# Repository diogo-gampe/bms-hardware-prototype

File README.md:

## Desenvolvimento em KICAD de placa de avaliação do CI da Texas Instrumets BQ769x2 para monitoramento e proteção de batérias de íon-lítio 3S-16S.

## Changelog

12/12/25
- Separa folha de monitoramento, folha de proteção e folha raiz
- (Folha raiz)Adiciona conector para resistores shunt de simulação de células
- (Folha de monitoramento) Adiciona botão de WAKE no pino TS2 do CI e jumper para conectar termistor externo ao pino TS2
- (Folha de monitoramento) Adiciona conector para monitorar externamente tensões geradas por regulador interno do CI em REG1 e REG2.
- (Folha de proteção) Adiciona componentes para circuito de disparo de fusível controlável
- (Folha de proteção) Adiciona componentes para circuito de pré-carga/descarga
- (Folha de proteção) Adciona componentes para proteção de conexão com polaridade reversa

18/12/25
- Adiciona diretório com simulações de LTSpice
28/01/25
- Adiciona footprints finais, com base na lista de componentes fornecidas ao pessoal do SENAI
- Posiciona Net-Tie entre terminal negativo da bateria e tensão de referência dos CIs para isolar caminhos de alta corrente
30/01/25
- Posiciona footprints de testpoints para medições de sinais chave para testes. 
- Ajusta posicionamento de regiões de alta corrente.

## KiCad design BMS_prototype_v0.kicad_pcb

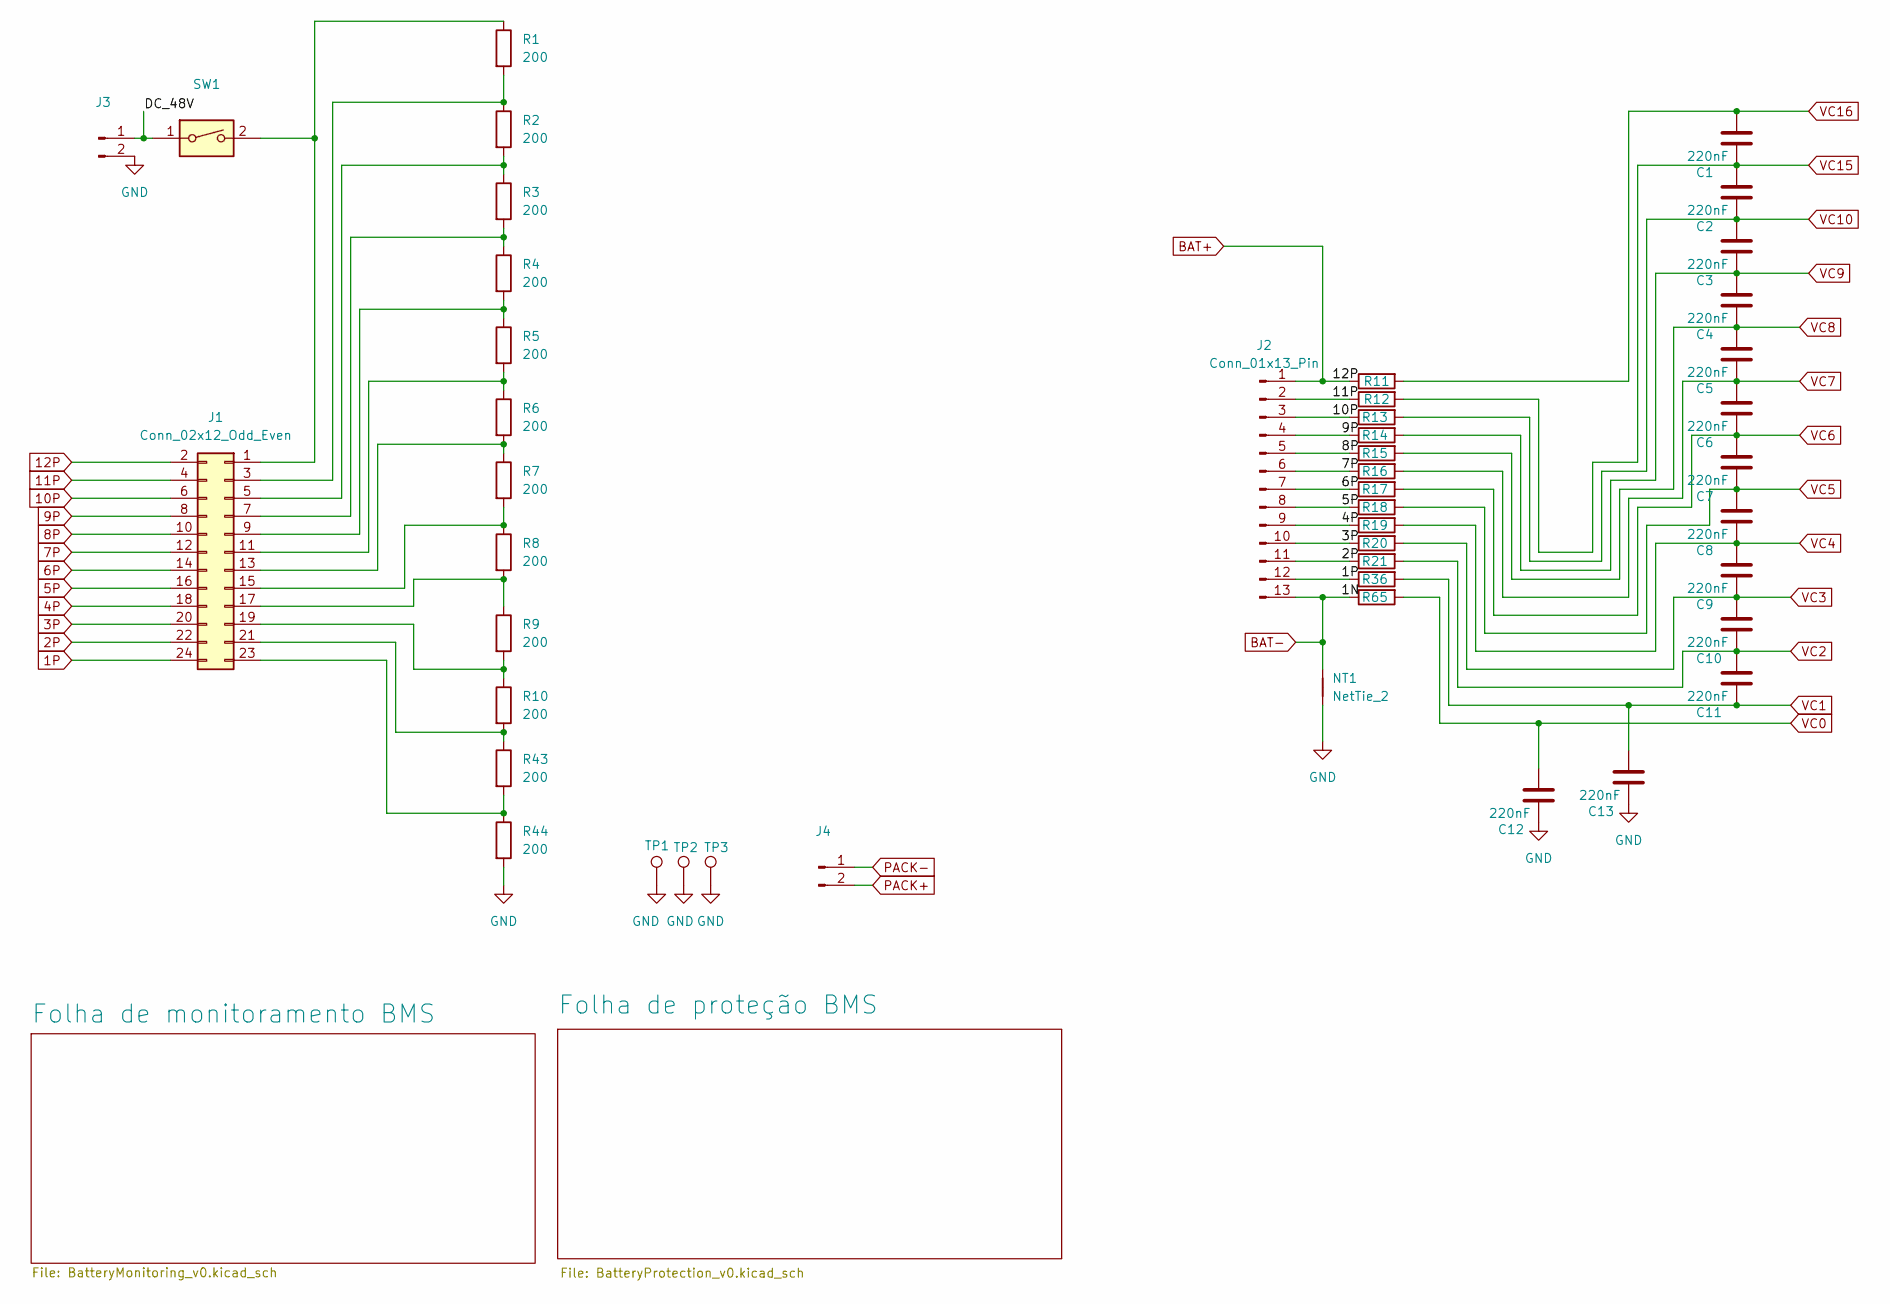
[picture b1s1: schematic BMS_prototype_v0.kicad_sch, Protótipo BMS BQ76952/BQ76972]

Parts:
C1, C2, C3, C4, C5, C6, C7, C8, C9, C10, C11, C12, C13: 220nF; C_1206_3216Metric_Pad1.33x1.80mm_HandSolder; Manufacturer_Part_Number C1206C224J5RECAUTO
J1: Conn_02x12_Odd_Even; PinHeader_2x12_P2.54mm_Vertical; Manufacturer_Part_Number G800W268018EU
J2: Conn_01x13_Pin; PinHeader_1x13_P2.54mm_Vertical; Manufacturer_Part_Number PH1-13-UA
J3: Conn_01x02_Pin; PinHeader_1x02_P2.54mm_Vertical; Manufacturer_Part_Number G800W306018EU
J4: Conn_01x02_Pin; CONN_1935776_PXC; Manufacturer_Part_Number G800W306018EU
NT1: NetTie_2; NetTie-2_SMD_Pad0.5mm
R1, R2, R3, R4, R5, R6, R7, R8, R9, R10, R43, R44: 200; R_1206_3216Metric; Manufacturer_Part_Number CR1206-FX-2000ELF
R11, R12, R13, R14, R15, R16, R17, R18, R19, R20, R21, R36, R65: 20; R_1206_3216Metric; Manufacturer_Part_Number RC1206FR-0720RL
SW1: SW_DIP_x01; SWT31AAA3S1; Manufacturer_Part_Number SW-T3-1A-A-A3-S1
TP1, TP2, TP3: TestPoint; TestPoint_Pad_3.0x3.0mm

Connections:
1P: J1.24, J2.12, R36.1
2P: J1.22, J2.11, R21.1
3P: J1.20, J2.10, R20.1
4P: J1.18, J2.9, R19.1
5P: J1.16, J2.8, R18.1
6P: J1.14, J2.7, R17.1
7P: J1.12, J2.6, R16.1
8P: J1.10, J2.5, R15.1
9P: J1.8, J2.4, R14.1
10P: J1.6, J2.3, R13.1
11P: J1.4, J2.2, R12.1
12P: J1.2, J2.1, R11.1; also elsewhere on the board
/DC_48V: J3.1, SW1.1
BAT-: J2.13, NT1.2, R65.1; also elsewhere on the board
GND: C12.2, C13.2, J3.2, NT1.1, R44.2, TP1.1, TP2.1, TP3.1; also elsewhere on the board
unnamed: J1.1, R1.1, SW1.2
unnamed: J1.3, R1.2, R2.1
unnamed: J1.5, R2.2, R3.1
unnamed: J1.7, R3.2, R4.1
unnamed: J1.9, R4.2, R5.1
unnamed: J1.11, R5.2, R6.1
unnamed: J1.13, R6.2, R7.1
unnamed: J1.15, R7.2, R8.1
unnamed: J1.17, R8.2, R9.1
unnamed: J1.19, R9.2, R10.1
unnamed: J1.21, R10.2, R43.1
unnamed: J1.23, R43.2, R44.1
PACK+: J4.2; also elsewhere on the board
PACK-: J4.1; also elsewhere on the board
VC0: C12.1, R65.2; also elsewhere on the board
VC1: C11.2, C13.1, R36.2; also elsewhere on the board
VC2: C10.2, C11.1, R21.2; also elsewhere on the board
VC3: C9.2, C10.1, R20.2; also elsewhere on the board
VC4: C8.2, C9.1, R19.2; also elsewhere on the board
VC5: C7.2, C8.1, R18.2; also elsewhere on the board
VC6: C6.2, C7.1, R17.2; also elsewhere on the board
VC7: C5.2, C6.1, R16.2; also elsewhere on the board
VC8: C4.2, C5.1, R15.2; also elsewhere on the board
VC9: C3.2, C4.1, R14.2; also elsewhere on the board
VC10: C2.2, C3.1, R13.2; also elsewhere on the board
VC15: C1.2, C2.1, R12.2; also elsewhere on the board
VC16: C1.1, R11.2; also elsewhere on the board

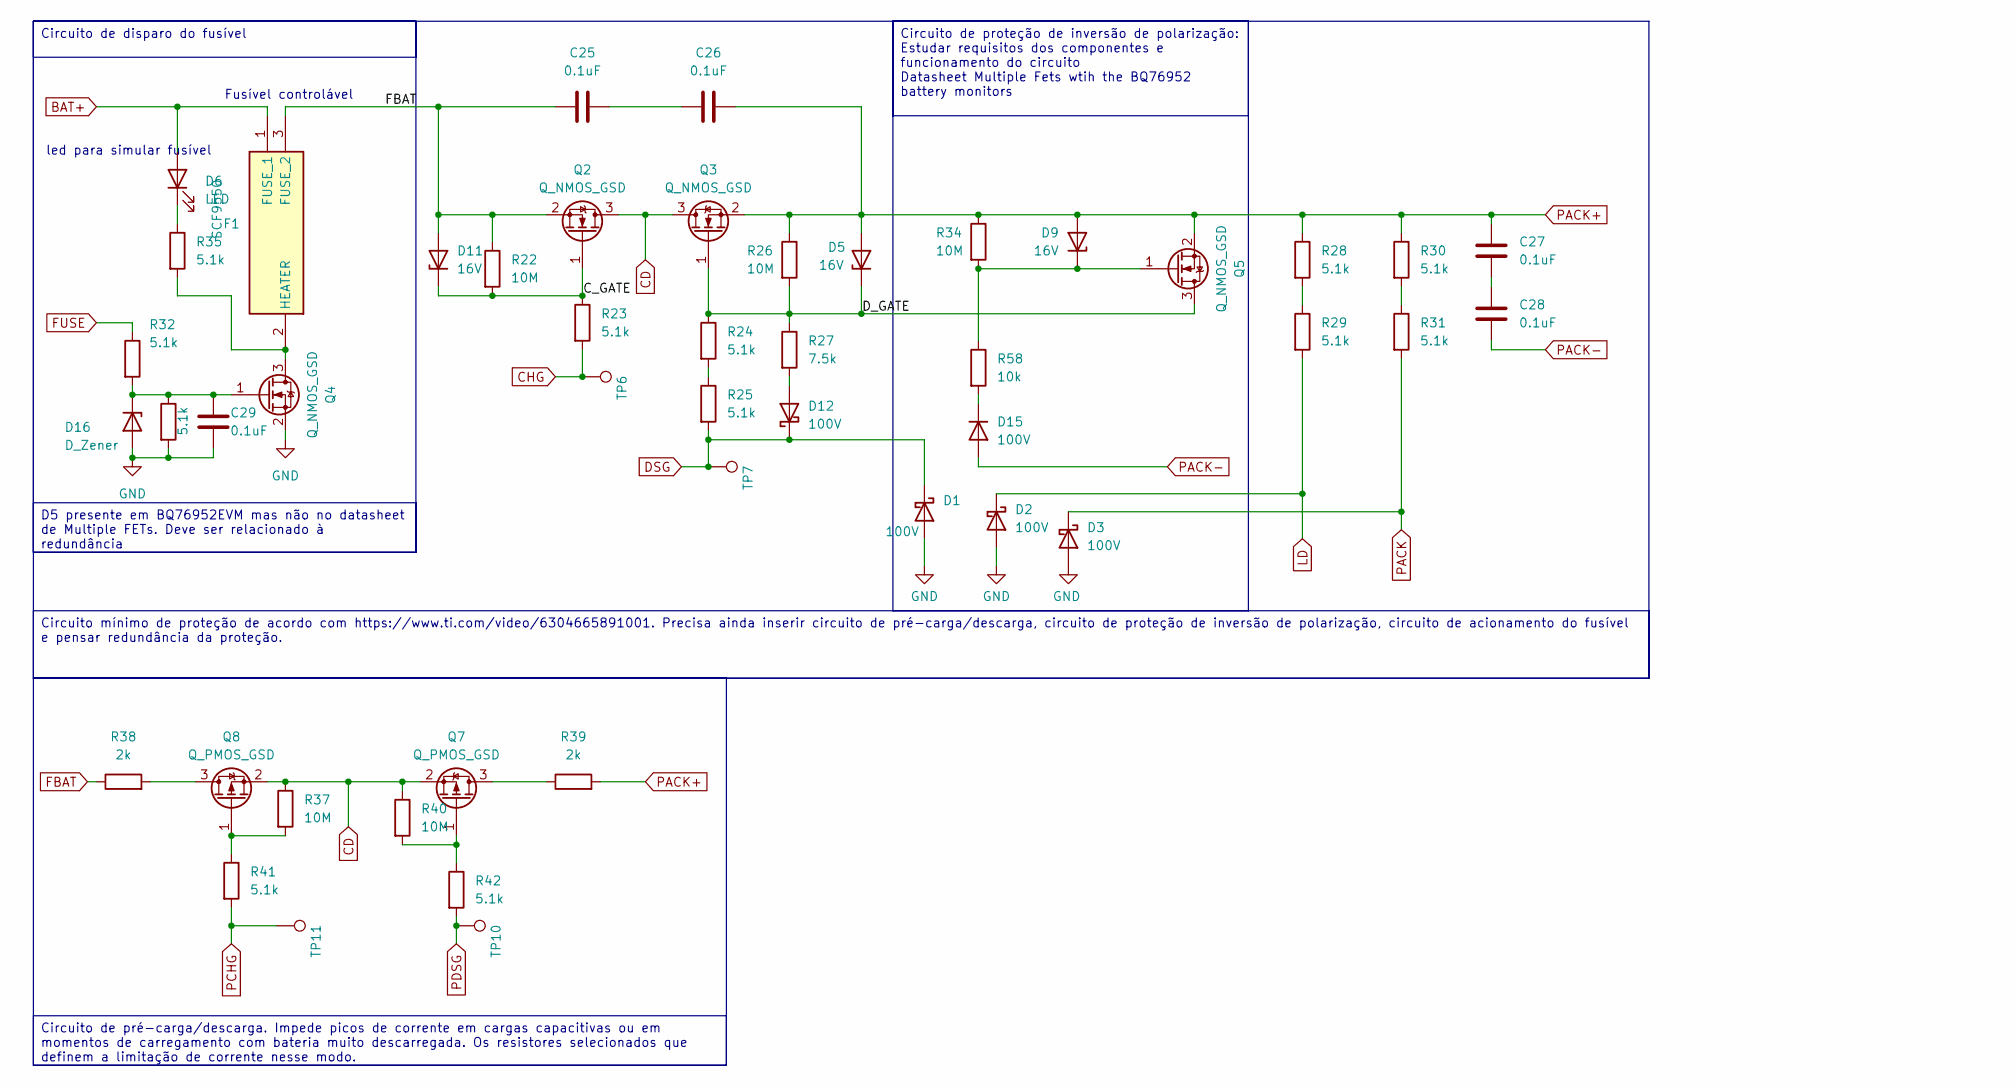
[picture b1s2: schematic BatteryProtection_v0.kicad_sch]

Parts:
C25, C26, C27, C28, C29: 0.1uF; C_1206_3216Metric_Pad1.33x1.80mm_HandSolder; Manufacturer_Part_Number C1206C104K5RACTU
D1, D2, D3, D12: 100V; D_SOD-123; Manufacturer_Part_Number BAT46W-7-F
D5, D9, D11: 16V; D_SOD-123; Manufacturer_Part_Number MMSZ5246B-TP
D6: LED; LED_1210_3225Metric; Manufacturer_Part_Number SML-LX1210IGC-TR
D15: 100V; SOT-23; Manufacturer_Part_Number MMBD914LT3G
D16: D_Zener; D_SOD-123; Manufacturer_Part_Number MMSZ4697T1G
F1: SCF9550; Sem título; Mouser Part Number 650-ITV4030L1412NR
Q2, Q3, Q5: Q_NMOS_GSD; TO-252-3_TabPin2; Manufacturer_Part_Number IPD200N15N3GATMA1
Q4: Q_NMOS_GSD; TO-252-3_TabPin2; Manufacturer_Part_Number AOD256
Q7, Q8: Q_PMOS_GSD; TSOP-6_1.65x3.05mm_P0.95mm; Manufacturer_Part_Number SI3437DV-T1-GE3
R22, R26, R34, R37, R40: 10M; R_1206_3216Metric; Manufacturer_Part_Number HV732BTTD1005F
R23, R24, R25, R28, R29, R30, R31, R32, R33, R35, R41, R42: 5.1k; R_1206_3216Metric; Manufacturer_Part_Number CRCW12065K10FKEAHP
R27: 7.5k; R_1206_3216Metric; Manufacturer_Part_Number RNCP1206FTD7K50
R38, R39: 2k; R_1206_3216Metric; Manufacturer_Part_Number HRG3216P-2001-D-T1
R58: 10k; R_1206_3216Metric; Manufacturer_Part_Number ERJ-8GEYJ103V
TP6, TP7, TP10, TP11: TestPoint; TestPoint_Loop_D3.80mm_Drill2.5mm

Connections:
12P: D6.2 (A), F1.1 (FUSE_1); also elsewhere on the board
/Folha de proteção BMS/C_GATE: D11.1 (K), Q2.1 (G), R22.2, R23.1
/Folha de proteção BMS/D_GATE: D5.1 (K), Q3.1 (G), Q5.3 (D), R24.1, R26.2, R27.1
CD: Q2.3 (D), Q3.3 (D), Q7.2 (S), Q8.2 (S), R37.1, R40.1; also elsewhere on the board
CHG: R23.2, TP6.1; also elsewhere on the board
DSG: D1.1 (K), D12.1 (K), R25.2, TP7.1; also elsewhere on the board
FBAT: C25.1, D11.2 (A), F1.3 (FUSE_2), Q2.2 (S), R22.1, R38.1
FUSE: R32.1; also elsewhere on the board
GND: C29.1, D1.2 (A), D2.2 (A), D3.2 (A), D16.2 (A), Q4.2 (S), R33.2; also elsewhere on the board
LD: D2.1 (K), R29.2; also elsewhere on the board
unnamed: C25.2, C26.1
unnamed: C27.1, C28.2
unnamed: D6.1 (K), R35.1
unnamed: D9.1 (K), Q5.1 (G), R34.2, R58.1
unnamed: D12.2 (A), R27.2
unnamed: D15.1 (K), R58.2
unnamed: C29.2, D16.1 (K), Q4.1 (G), R32.2, R33.1
unnamed: F1.2 (HEATER), Q4.3 (D), R35.2
unnamed: Q7.3 (D), R39.1
unnamed: Q7.1 (G), R40.2, R42.1
unnamed: Q8.3 (D), R38.2
unnamed: Q8.1 (G), R37.2, R41.1
unnamed: R24.2, R25.1
unnamed: R28.2, R29.1
unnamed: R30.2, R31.1
PACK: D3.1 (K), R31.2; also elsewhere on the board
PACK+: C26.2, C27.2, D5.2 (A), D9.2 (A), Q3.2 (S), Q5.2 (S), R26.1, R28.1, R30.1, R34.1, R39.2; also elsewhere on the board
PACK-: C28.1, D15.2 (A); also elsewhere on the board
PCHG: R41.2, TP11.1; also elsewhere on the board
PDSG: R42.2, TP10.1; also elsewhere on the board

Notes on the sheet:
led para simular fusível
Fusível controlável
Circuito de proteção de inversão de polarização: Estudar requisitos dos componentes e funcionamento do circuito Datasheet Multiple Fets wtih the BQ76952 battery monitors
Circuito mínimo de proteção de acordo com https://www.ti.com/video/6304665891001. Precisa ainda inserir circuito de pré-carga/descarga, circuito de proteção de inversão de polarização, circuito de acionamento do fusível e pensar redundância da proteção.
D5 presente em BQ76952EVM mas não no datasheet de Multiple FETs. Deve ser relacionado à redundância
Circuito de disparo do fusível
Circuito de pré-carga/descarga. Impede picos de corrente em cargas capacitivas ou em momentos de carregamento com bateria muito descarregada. Os resistores selecionados que definem a limitação de corrente nesse modo.

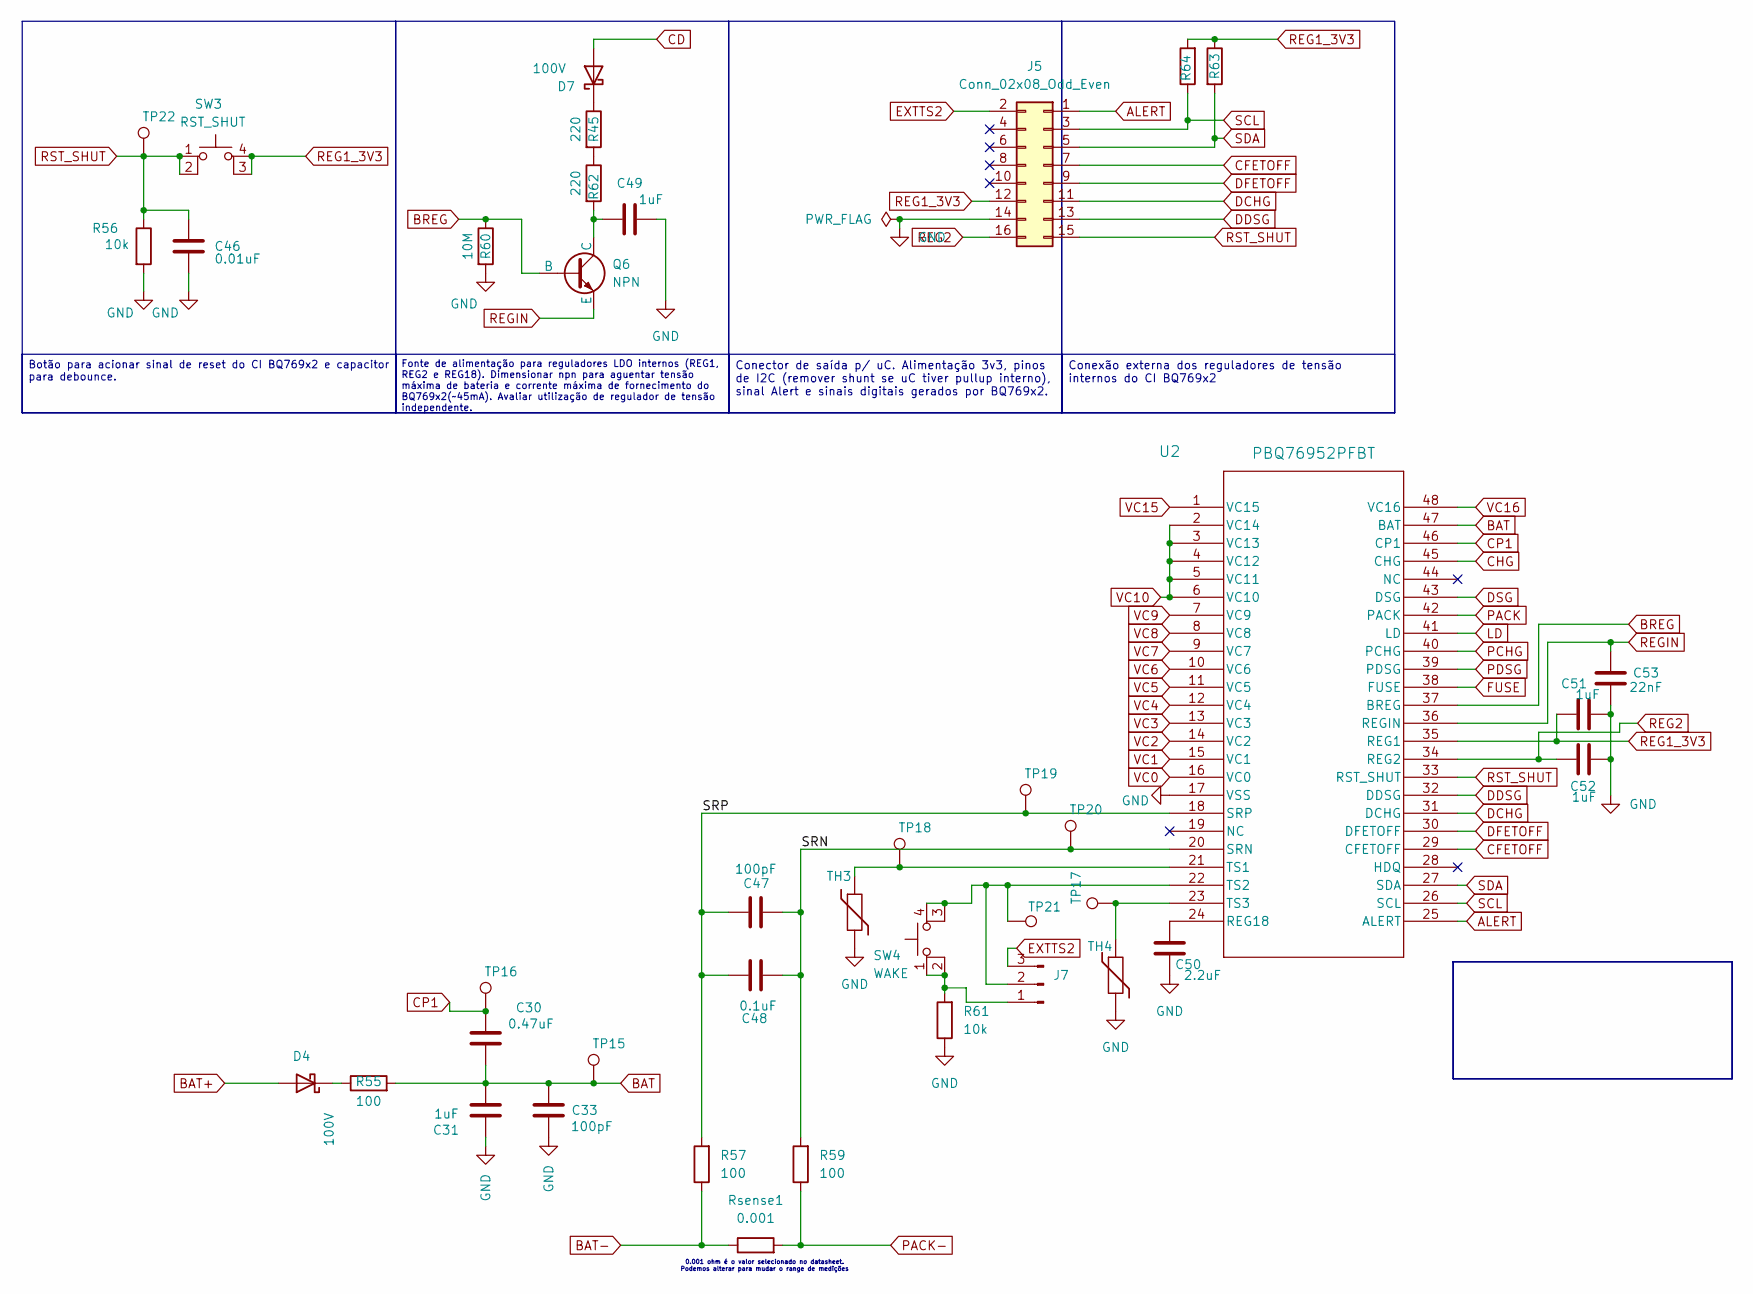
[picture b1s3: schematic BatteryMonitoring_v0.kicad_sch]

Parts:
C30: 0.47uF; C_1206_3216Metric_Pad1.33x1.80mm_HandSolder; Manufacturer_Part_Number CL31B474KBHNNNE
C31, C49, C51, C52: 1uF; C_1206_3216Metric_Pad1.33x1.80mm_HandSolder; Manufacturer_Part_Number CL31B105KBHNNNE
C33, C47: 100pF; C_1206_3216Metric_Pad1.33x1.80mm_HandSolder; Manufacturer_Part_Number VPDD102W101K1GV001E
C46: 0.01uF; C_1206_3216Metric_Pad1.33x1.80mm_HandSolder; Manufacturer_Part_Number 1206PC103KAT2A
C48: 0.1uF; C_1206_3216Metric_Pad1.33x1.80mm_HandSolder; Manufacturer_Part_Number C1206C104K5RACTU
C50: 2.2uF; C_1206_3216Metric_Pad1.33x1.80mm_HandSolder; Manufacturer_Part_Number CL31B225KBHNNNE
C53: 22nF; C_1206_3216Metric_Pad1.33x1.80mm_HandSolder; Manufacturer_Part_Number CC1206JRNPO9BN223
D4, D7: 100V; D_SOD-123; Manufacturer_Part_Number BAT46W-7-F
J5: Conn_02x08_Odd_Even; CONN16_SBH11-PBPC-D08-ST-BK_SUL; Manufacturer_Part_Number SBH11-PBPC-D08-ST-BK
J7: Conn_01x03_Pin; PinSocket_1x03_P2.54mm_Vertical; Manufacturer_Part_Number 2011-1X03G00SB-1
Q6: NPN; TO-92; Manufacturer_Part_Number 2N5830
R45, R62: 220; R_1206_3216Metric; Manufacturer_Part_Number CRCW2512220RJNEG
R55, R57, R59: 100; R_1206_3216Metric; Manufacturer_Part_Number RC1206FR-07100RL
R56, R61: 10k; R_1206_3216Metric; Manufacturer_Part_Number ERJ-8GEYJ103V
R60: 10M; R_1206_3216Metric; Manufacturer_Part_Number HV732BTTD1005F
R63, R64: 20; R_1206_3216Metric; Manufacturer_Part_Number RC1206FR-0720RL
Rsense1: 0.001; S200_75
SW3: RST_SHUT; SMT_FS; Manufacturer_Part_Number PTS526SM15SMTR2 LFS
SW4: WAKE; SMT_FS; Manufacturer_Part_Number PTS526SK15SMTR2 LFS
TH3, TH4: Thermistor; 103AT2; Manufacturer_Part_Number 103AT-2
TP15, TP16, TP17, TP18, TP19, TP20, TP21, TP22: TestPoint; TestPoint_Loop_D3.80mm_Drill2.5mm
U2: PBQ76952PFBT; BQ7692_TEX; Manufacturer_Part_Number BQ7695202PFBR

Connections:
12P: D4.2 (A); also elsewhere on the board
/Folha de monitoramento BMS/SRN: C47.2, C48.2, R59.2, TP20.1, U2.20 (SRN)
/Folha de monitoramento BMS/SRP: C47.1, C48.1, R57.2, TP19.1, U2.18 (SRP)
ALERT: J5.1, U2.25 (ALERT)
BAT: C30.2, C31.1, C33.1, R55.2, TP15.1, U2.47 (BAT)
BAT-: R57.1, Rsense1.1; also elsewhere on the board
BREG: Q6.2 (B), R60.1, U2.37 (BREG)
CD: D7.2 (A); also elsewhere on the board
CFETOFF: J5.7, U2.29 (CFETOFF)
CHG: U2.45 (CHG); also elsewhere on the board
CP1: C30.1, TP16.1, U2.46 (CP1)
DCHG: J5.11, U2.31 (DCHG)
DDSG: J5.13, U2.32 (DDSG)
DFETOFF: J5.9, U2.30 (DFETOFF)
DSG: U2.43 (DSG); also elsewhere on the board
EXTTS2: J5.2, J7.3
FUSE: U2.38 (FUSE); also elsewhere on the board
GND: C31.2, C33.2, C46.2, C49.2, C50.1, C51.1, C52.1, C53.2, J5.14, R56.2, R60.2, R61.1, TH3.2, TH4.2, U2.17 (VSS); also elsewhere on the board
LD: U2.41 (LD); also elsewhere on the board
unnamed: D4.1 (K), R55.1
unnamed: D7.1 (K), R45.1
unnamed: J7.1, R61.2, SW4.1, SW4.2
unnamed: J7.2, SW4.3 (K), SW4.4 (A), TP21.1, U2.22 (TS2)
unnamed: C49.1, Q6.1 (C), R62.2
unnamed: R45.2, R62.1
unnamed: C50.2, U2.24 (REG18)
unnamed: TH3.1, TP18.1, U2.21 (TS1)
unnamed: TH4.1, TP17.1, U2.23 (TS3)
PACK: U2.42 (PACK); also elsewhere on the board
PACK-: R59.1, Rsense1.2; also elsewhere on the board
PCHG: U2.40 (PCHG); also elsewhere on the board
PDSG: U2.39 (PDSG); also elsewhere on the board
REG1_3V3: C51.2, J5.12, R63.1, R64.2, SW3.3 (K), SW3.4 (A), U2.35 (REG1)
REG2: C52.2, J5.16, U2.34 (REG2)
REGIN: C53.1, Q6.3 (E), U2.36 (REGIN)
RST_SHUT: C46.1, J5.15, R56.1, SW3.1, SW3.2, TP22.1, U2.33 (RST_SHUT)
SCL: J5.3, R64.1, U2.26 (SCL)
SDA: J5.5, R63.2, U2.27 (SDA)
VC0: U2.16 (VC0); also elsewhere on the board
VC1: U2.15 (VC1); also elsewhere on the board
VC2: U2.14 (VC2); also elsewhere on the board
VC3: U2.13 (VC3); also elsewhere on the board
VC4: U2.12 (VC4); also elsewhere on the board
VC5: U2.11 (VC5); also elsewhere on the board
VC6: U2.10 (VC6); also elsewhere on the board
VC7: U2.9 (VC7); also elsewhere on the board
VC8: U2.8 (VC8); also elsewhere on the board
VC9: U2.7 (VC9); also elsewhere on the board
VC10: U2.2 (VC14), U2.3 (VC13), U2.4 (VC12), U2.5 (VC11), U2.6 (VC10); also elsewhere on the board
VC15: U2.1 (VC15); also elsewhere on the board
VC16: U2.48 (VC16); also elsewhere on the board

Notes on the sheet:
0.001 ohm é o valor selecionado no datasheet. Podemos alterar para mudar o range de medições
Conector de saída p/ uC. Alimentação 3v3, pinos de I2C (remover shunt se uC tiver pullup interno), sinal Alert e sinais digitais gerados por BQ769x2.
Botão para acionar sinal de reset do CI BQ769x2 e capacitor para debounce.
Conexão externa dos reguladores de tensão internos do CI BQ769x2
Fonte de alimentação para reguladores LDO internos (REG1, REG2 e REG18). Dimensionar npn para aguentar tensão máxima de bateria e corrente máxima de fornecimento do BQ769x2(~45mA). Avaliar utilização de regulador de tensão independente.

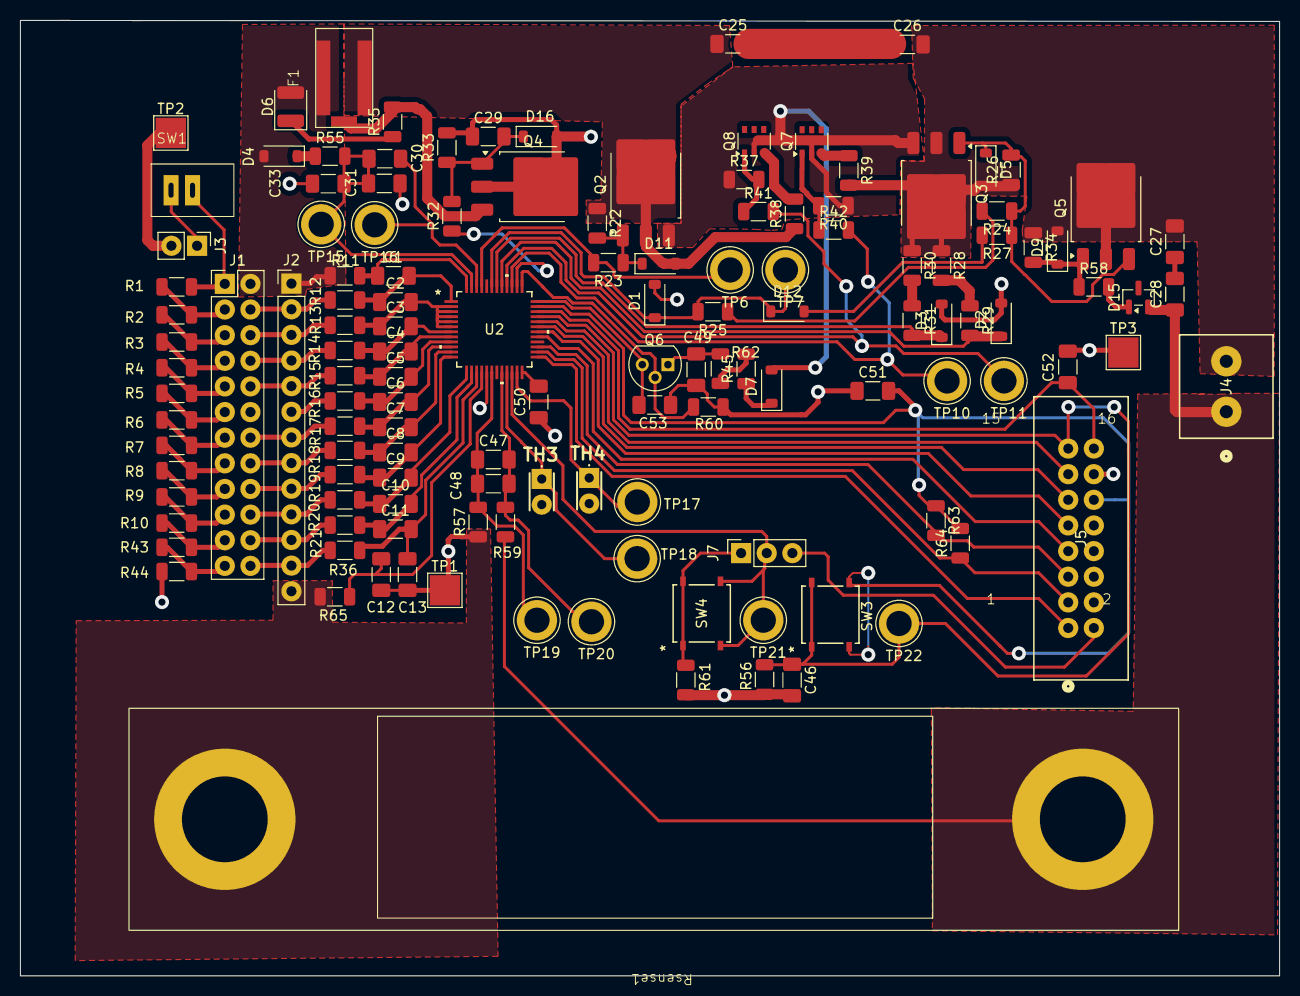
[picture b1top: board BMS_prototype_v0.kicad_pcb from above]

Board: 2 copper layers, 124.8 x 94.7 mm, 134 parts (0 on the bottom side), 94 nets.

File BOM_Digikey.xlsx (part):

Reference | Value | Qty | Digikey Link | Manufacturer_Part_Number
 | STM32H745ZIT3 | 5 | https://www.digikey.ca/en/products/detail/stmicroelectronics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 | STM32H745ZIT3
 | BQ76972PFBR | 5 | https://www.digikey.ca/en/products/detail/texas-instruments/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 | BQ7697202PFBR
U2 | BQ7695202PFBR | 5 | https://www.digikey.ca/en/products/detail/texas-instruments/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 | BQ7695202PFBR
 | TJA1044BT/0Z | 5 | https://www.digikey.ca/en/products/detail/nxp-usa-inc/TJA104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 | TJA1044BT/0Z
C47 | 100pF | 5 | https://www.digikey.ca/en/products/detail/johanson-dielectri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 | VPDD102W101K1GV001E
C33 | 100pF | 5 | https://www.digikey.ca/en/products/detail/johanson-dielectri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 | VPDD102W101K1GV001E
SW1 | SW_DIP_x01 | 5 | https://www.digikey.ca/en/products/detail/adam-tech/SW-T3-1A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 | SW-T3-1A-A-A3-S1
D6 | LED | 5 | https://www.digikey.ca/en/products/detail/lumex-opto-compone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 | SML-LX1210IGC-TR
Q8 | Q_PMOS_GSD | 5 | https://www.digikey.ca/en/products/detail/vishay-siliconix/S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 | SI3437DV-T1-GE3
Q7 | Q_PMOS_GSD | 5 | https://www.digikey.ca/en/products/detail/vishay-siliconix/S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 | SI3437DV-T1-GE3
J5 | Conn_02x08_Odd_Even | 5 | https://www.digikey.ca/en/products/detail/sullins-connector-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 | SBH11-PBPC-D08-ST-BK
R27 | 7.5k | 5 | https://www.digikey.ca/en/products/detail/stackpole-electron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 | RNCP1206FTD7K50
R59 | 100 | 5 | https://www.digikey.ca/en/products/detail/yageo/RC1206FR-071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 | RC1206FR-07100RL
R57 | 100 | 5 | https://www.digikey.ca/en/products/detail/yageo/RC1206FR-071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 | RC1206FR-07100RL
R55 | 100 | 5 | https://www.digikey.ca/en/products/detail/yageo/RC1206FR-071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 | RC1206FR-07100RL
R65 | 20 | 5 | https://www.digikey.ca/en/products/detail/yageo/RC1206FR-072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 | RC1206FR-0720RL
R64 | 20 | 5 | https://www.digikey.ca/en/products/detail/yageo/RC1206FR-072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 | RC1206FR-0720RL
R63 | 20 | 5 | https://www.digikey.ca/en/products/detail/yageo/RC1206FR-072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 | RC1206FR-0720RL
R36 | 20 | 5 | https://www.digikey.ca/en/products/detail/yageo/RC1206FR-072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 | RC1206FR-0720RL
R21 | 20 | 5 | https://www.digikey.ca/en/products/detail/yageo/RC1206FR-072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 | RC1206FR-0720RL
R20 | 20 | 5 | https://www.digikey.ca/en/products/detail/yageo/RC1206FR-072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 | RC1206FR-0720RL
R19 | 20 | 5 | https://www.digikey.ca/en/products/detail/yageo/RC1206FR-072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 | RC1206FR-0720RL
R18 | 20 | 5 | https://www.digikey.ca/en/products/detail/yageo/RC1206FR-072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 | RC1206FR-0720RL
R17 | 20 | 5 | https://www.digikey.ca/en/products/detail/yageo/RC1206FR-072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 | RC1206FR-0720RL
R16 | 20 | 5 | https://www.digikey.ca/en/products/detail/yageo/RC1206FR-072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 | RC1206FR-0720RL
R15 | 20 | 5 | https://www.digikey.ca/en/products/detail/yageo/RC1206FR-072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 | RC1206FR-0720RL
R14 | 20 | 5 | https://www.digikey.ca/en/products/detail/yageo/RC1206FR-072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 | RC1206FR-0720RL
R13 | 20 | 5 | https://www.digikey.ca/en/products/detail/yageo/RC1206FR-072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 | RC1206FR-0720RL
R12 | 20 | 5 | https://www.digikey.ca/en/products/detail/yageo/RC1206FR-072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 | RC1206FR-0720RL
R11 | 20 | 5 | https://www.digikey.ca/en/products/detail/yageo/RC1206FR-072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 | RC1206FR-0720RL
SW3 | RST_SHUT | 5 | https://www.digikey.ca/en/products/detail/c-k/PTS526SM15SMTR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 | PTS526SM15SMTR2 LFS
SW4 | WAKE | 5 | https://www.digikey.ca/en/products/detail/c-k/PTS526SM15SMTR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 | PTS526SK15SMTR2 LFS
J2 | Conn_01x13_Pin | 5 | https://www.digikey.ca/en/products/detail/adam-tech/PH1-13-U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 | PH1-13-UA
D16 | D_Zener | 5 | https://www.digikey.ca/en/products/detail/onsemi/MMSZ4697T1G/919730 | MMSZ4697T1G
D11 | 16V | 5 | https://www.digikey.ca/en/products/detail/mcc-micro-commerci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 | MMSZ5246B-TP
D9 | 16V | 5 | https://www.digikey.ca/en/products/detail/mcc-micro-commerci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 | MMSZ5246B-TP
D5 | 16V | 5 | https://www.digikey.ca/en/products/detail/mcc-micro-commerci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 | MMSZ5246B-TP
D15 | 100V | 5 | https://www.digikey.ca/en/products/detail/onsemi/MMBD914LT3G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 | MMBD914LT3G
F1 | SCF9550-30-20L | 5 | https://www.digikey.ca/en/products/detail/eaton-electronics-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 | SCF9550-30-20L
Q5 | Q_NMOS_GSD | 5 | https://www.digikey.ca/en/products/detail/infineon-technolog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 | IPD200N15N3GATMA1
Q3 | Q_NMOS_GSD | 5 | https://www.digikey.ca/en/products/detail/infineon-technolog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 | IPD200N15N3GATMA1
Q2 | Q_NMOS_GSD | 5 | https://www.digikey.ca/en/products/detail/infineon-technolog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 | IPD200N15N3GATMA1
R60 | 10M | 5 | https://www.digikey.ca/en/products/detail/koa-speer-electron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 | HV732BTTD1005F
R40 | 10M | 5 | https://www.digikey.ca/en/products/detail/koa-speer-electron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 | HV732BTTD1005F
R37 | 10M | 5 | https://www.digikey.ca/en/products/detail/koa-speer-electron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 | HV732BTTD1005F
R34 | 10M | 5 | https://www.digikey.ca/en/products/detail/koa-speer-electron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 | HV732BTTD1005F
R26 | 10M | 5 | https://www.digikey.ca/en/products/detail/koa-speer-electron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 | HV732BTTD1005F
R22 | 10M | 5 | https://www.digikey.ca/en/products/detail/koa-speer-electron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 | HV732BTTD1005F
R39 | 2k | 5 | https://www.digikey.ca/en/products/detail/susumu/HRG3216P-20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 | HRG3216P-2001-D-T1
R38 | 2k | 5 | https://www.digikey.ca/en/products/detail/susumu/HRG3216P-20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 | HRG3216P-2001-D-T1
J4 | Conn_01x02_Pin |  | https://www.digikey.ca/en/products/detail/phoenix-contact/19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 | 1935776
J3 | Conn_01x02_Pin | 5 | https://www.digikey.ca/en/products/detail/amphenol-cs-commer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 | G800W306018EU
J1 | Conn_02x12_Odd_Even | 5 | https://www.digikey.ca/en/products/detail/amphenol-cs-commer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 | G800W268018EU
R61 | 10k | 5 | https://www.digikey.ca/en/products/detail/panasonic-electron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 | ERJ-8GEYJ103V
R58 | 10k | 5 | https://www.digikey.ca/en/products/detail/panasonic-electron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 | ERJ-8GEYJ103V
R56 | 10k | 5 | https://www.digikey.ca/en/products/detail/panasonic-electron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 | ERJ-8GEYJ103V
R42 | 5.1k | 5 | https://www.digikey.ca/en/products/detail/vishay-dale/CRCW12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 | CRCW12065K10FKEAHP
R41 | 5.1k | 5 | https://www.digikey.ca/en/products/detail/vishay-dale/CRCW12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 | CRCW12065K10FKEAHP
R35 | 5.1k | 5 | https://www.digikey.ca/en/products/detail/vishay-dale/CRCW12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 | CRCW12065K10FKEAHP
R33 | 5.1k | 5 | https://www.digikey.ca/en/products/detail/vishay-dale/CRCW12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 | CRCW12065K10FKEAHP
R32 | 5.1k | 5 | https://www.digikey.ca/en/products/detail/vishay-dale/CRCW12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 | CRCW12065K10FKEAHP
R31 | 5.1k | 5 | https://www.digikey.ca/en/products/detail/vishay-dale/CRCW12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 | CRCW12065K10FKEAHP
R30 | 5.1k | 5 | https://www.digikey.ca/en/products/detail/vishay-dale/CRCW12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 | CRCW12065K10FKEAHP
R29 | 5.1k | 5 | https://www.digikey.ca/en/products/detail/vishay-dale/CRCW12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 | CRCW12065K10FKEAHP
R28 | 5.1k | 5 | https://www.digikey.ca/en/products/detail/vishay-dale/CRCW12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 | CRCW12065K10FKEAHP
R25 | 5.1k | 5 | https://www.digikey.ca/en/products/detail/vishay-dale/CRCW12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 | CRCW12065K10FKEAHP
R24 | 5.1k | 5 | https://www.digikey.ca/en/products/detail/vishay-dale/CRCW12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 | CRCW12065K10FKEAHP
R23 | 5.1k | 5 | https://www.digikey.ca/en/products/detail/vishay-dale/CRCW12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 | CRCW12065K10FKEAHP
R62 | 220 | 5 | https://www.digikey.ca/en/products/detail/susumu/HRG3216P-22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 | HRG3216P-2200-B-T1
R45 | 220 | 5 | https://www.digikey.ca/en/products/detail/susumu/HRG3216P-22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 | CRCW2512220RJNEG
R44 | 220 | 5 | https://www.digikey.ca/en/products/detail/susumu/HRG3216P-22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 | CR1206-FX-2000ELF
R43 | 220 | 5 | https://www.digikey.ca/en/products/detail/susumu/HRG3216P-22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 | CR1206-FX-2000ELF
R10 | 220 | 5 | https://www.digikey.ca/en/products/detail/susumu/HRG3216P-22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 | CR1206-FX-2000ELF
R9 | 220 | 5 | https://www.digikey.ca/en/products/detail/susumu/HRG3216P-22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 | CR1206-FX-2000ELF
R8 | 220 | 5 | https://www.digikey.ca/en/products/detail/susumu/HRG3216P-22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 | CR1206-FX-2000ELF
R7 | 220 | 5 | https://www.digikey.ca/en/products/detail/susumu/HRG3216P-22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 | CR1206-FX-2000ELF
R6 | 220 | 5 | https://www.digikey.ca/en/products/detail/susumu/HRG3216P-22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 | CR1206-FX-2000ELF
R5 | 220 | 5 | https://www.digikey.ca/en/products/detail/susumu/HRG3216P-22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 | CR1206-FX-2000ELF
R4 | 220 | 5 | https://www.digikey.ca/en/products/detail/susumu/HRG3216P-22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 | CR1206-FX-2000ELF
R3 | 220 | 5 | https://www.digikey.ca/en/products/detail/susumu/HRG3216P-22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 | CR1206-FX-2000ELF
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
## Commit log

2025-12-04 add readme
2025-12-04 remove .txt
2025-12-05 Revisão de conexões
2025-12-08 Revisão
2025-12-08 Inserindo footprints
2025-12-10 adiciona folha do esquemático de proteção
2025-12-10 add esquemático de proteção
2025-12-12 adiciona folha de monitoramento, circuitos de protecao
2025-12-18 add diretorio de simulações
2026-01-13 add simulacao de carga/descarga
2026-01-20 Inicio do roteamento e posicionamento da PCB
2026-01-22 add Res Shunt e atualiza para Kicad 9.0
2026-01-23 Troca trilhas por regiões
2026-01-28 Layout com footprints dos componentes da lista
2026-01-28 layout final de componentes, com footprints da lista de componentes
2026-01-28 layout final de componentes, com footprints da lista de componentes mais uma adição de via GND
2026-01-30 posiciona testpoints
2026-02-09 Alterações realizadas por Eduardo
2026-02-09 Ajustes no layout do BMS
2026-02-12 salva 12/02
